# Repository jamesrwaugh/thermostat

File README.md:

# AVR Thermostat

James' interest in making a thermostat

# Features

- [End Goal] Home Assisstant integration compatible
- Plugs into residential connections offering 24VAC power
- Programmable time/day-based temperature settings
- Heating, cooling, and off modes
- Battery-backed storage for settings and time
- Support on-cool and on-heat reverse valve types
- Auto or always-on fan setting
- Display in Fahrenheit or Celsius
- ISP header for firmware flashing and updates
- Objectively gorgeous vacuum-florescent display
- Runs on a familiar, lovable AVR
- All this and more, in a small & tiny 16Kb firmware binary

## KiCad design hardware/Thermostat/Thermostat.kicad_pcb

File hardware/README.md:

# 2.0 Fixes

- [ ] Correct to 1mm hole sizes for screen connector
- [ ] Correct hole placement for buttons
- [ ] 10k Pull-up resistor on RXD of RS-485 (see datasheet)
- [ ] Use a dedicated flash chip, need more than 56 bytes of DS1307
- [ ] Use an analog temperature chip, I2C driver size for TMP116 is 500 bytes, or reduce code size

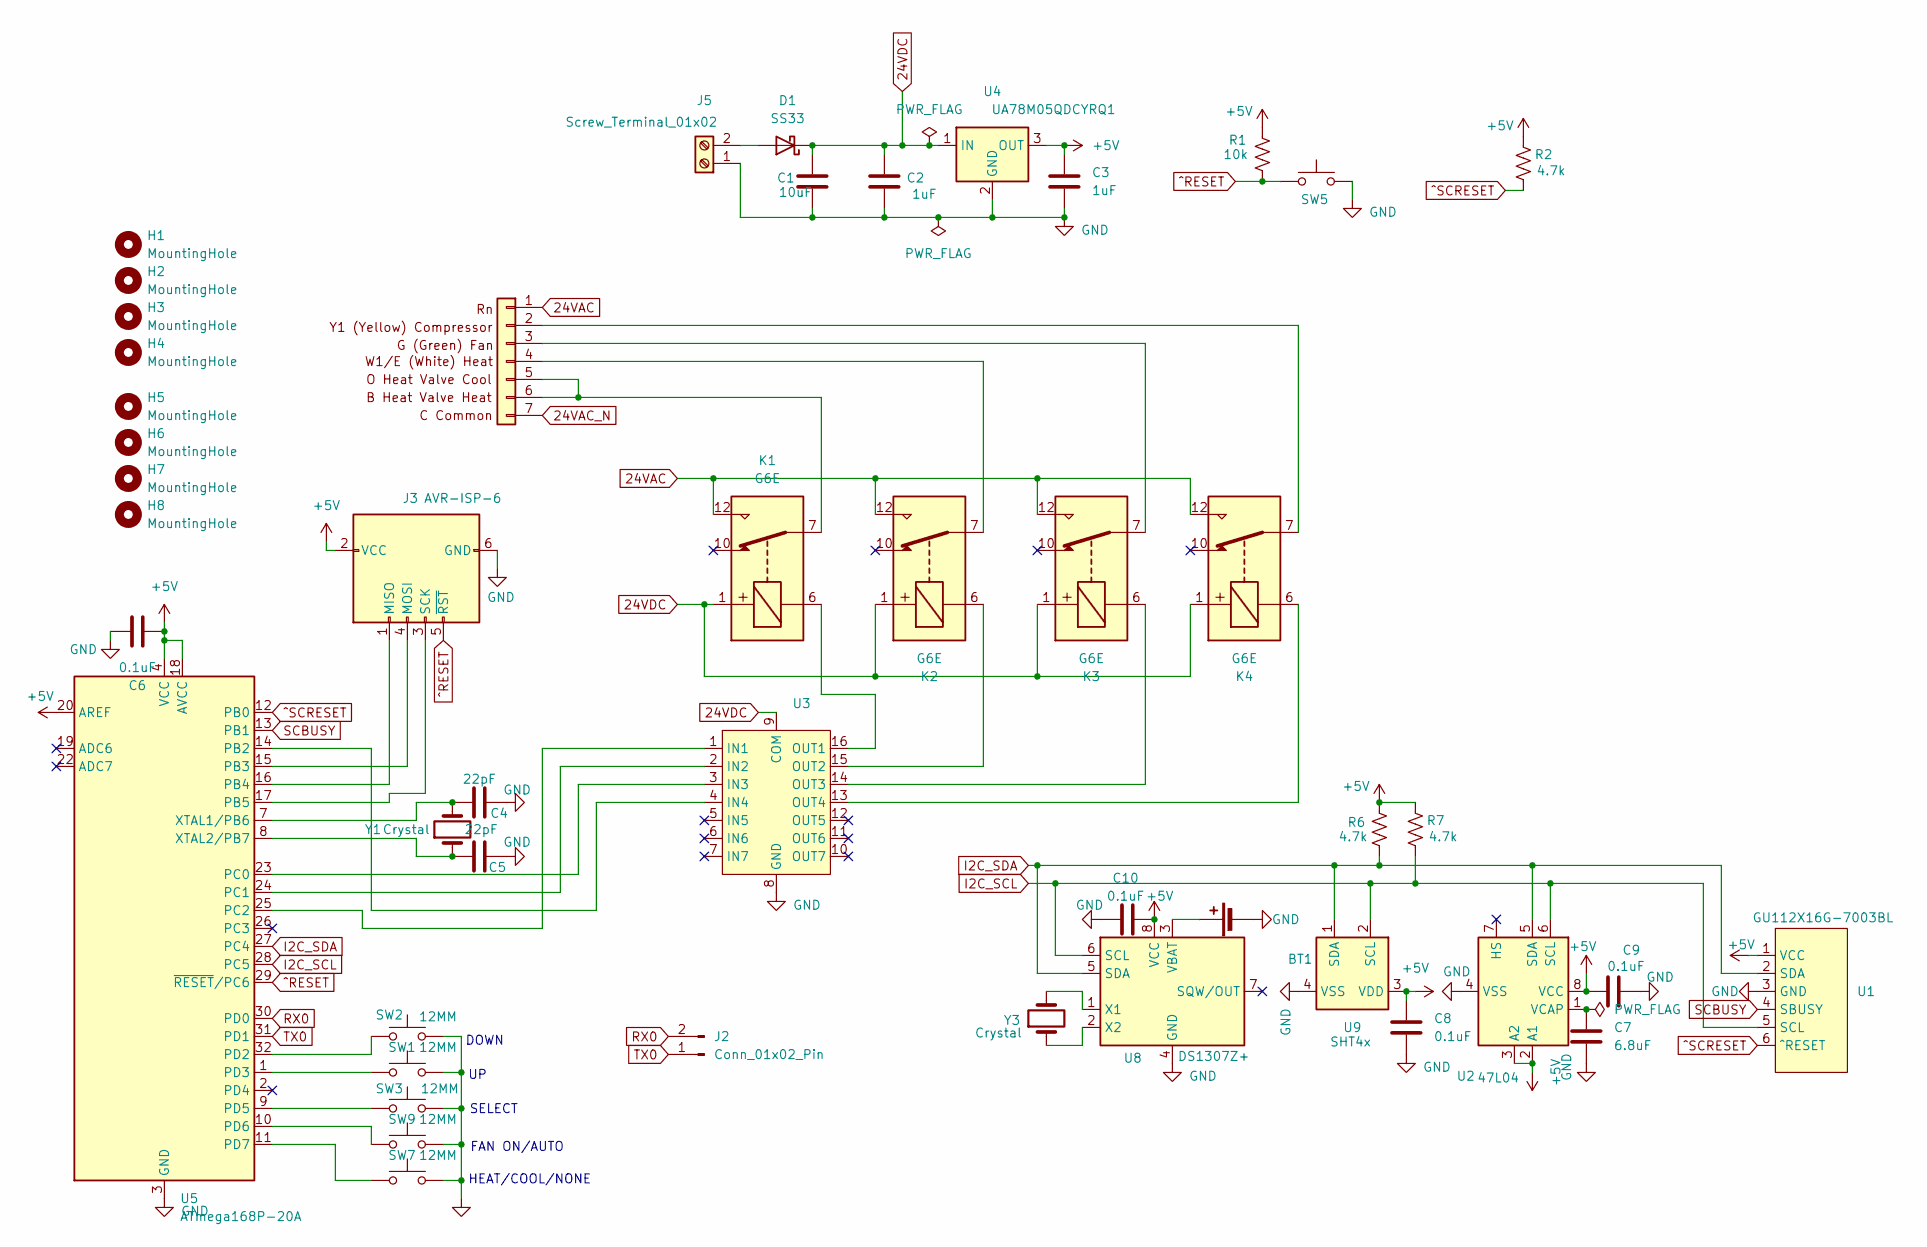
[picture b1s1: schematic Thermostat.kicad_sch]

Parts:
BT1: Battery_Cell; BS-12-B3AA011
C1: 10uF; C_1210_3225Metric
C2, C3: 1uF; C_1210_3225Metric
C4, C5: 22pF; C_0603_1608Metric
C6, C8, C9, C10: 0.1uF; C_0603_1608Metric
C7: 6.8uF; C_0603_1608Metric
D1: SS33; D_SMA
H1, H2, H3, H4: MountingHole; MountingHole_3mm
H5, H6, H7, H8: MountingHole; MountingHole_2mm
J2: Conn_01x02_Pin; PinHeader_1x02_P2.54mm_Vertical_SMD_Pin1Left
J3: AVR-ISP-6; PinHeader_2x03_P2.54mm_Vertical_SMD_2
J4: MainConnectorr; TerminalBlock_MaiXu_MX126-5.0-07P_1x07_P5.00mm
J5: Screw_Terminal_01x02; TerminalBlock_MetzConnect_Type094_RT03502HBLU_1x02_P5.00mm_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
K1, K2, K3, K4: G6E; Relay_SPDT_Omron_G6E
R1: 10k; R_0603_1608Metric
R2, R6, R7: 4.7k; R_0603_1608Metric
SW1, SW2, SW3, SW7, SW9: 12MM; B3F
SW5: SW_Push; SW_Push_1P1T_NO_CK_KMR2
U1: GU112X16G-7003BL; GU-7003
U2: 47L04; SOIC-8_3.9x4.9mm_P1.27mm
U3: SOIC-16_3.9x9.9mm_P1.27mm
U4: UA78M05QDCYRQ1; SOT-223-3_TabPin2
U5: ATmega168P-20A; TQFP-32_7x7mm_P0.8mm
U8: DS1307Z+; SOIC-8_3.9x4.9mm_P1.27mm
U9: SHT4x; Sensirion_DFN-4_1.5x1.5mm_P0.8mm_SHT4x_NoCentralPad
Y1: Crystal; Crystal_SMD_5032-2Pin_5.0x3.2mm
Y3: Crystal; Crystal_SMD_3215-2Pin_3.2x1.5mm

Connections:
24VAC: J4.1, K1.12, K2.12, K3.12, K4.12
24VAC_N: J4.7
24VDC: C1.1, C2.1, D1.1 (K), K1.1, K2.1, K3.1, K4.1, U3.9 (COM), U4.1 (IN)
+5V: C3.1, C6.1, C8.2, C9.2, C10.1, J3.2 (VCC), R1.1, R2.1, R6.1, R7.1, U1.1 (VCC), U2.2 (A1), U2.3 (A2), U2.8 (VCC), U4.3 (OUT), U5.4 (VCC), U5.6 (VCC), U5.18 (AVCC), U5.20 (AREF), U8.8 (VCC), U9.3 (VDD)
GND: BT1.2 (-), C1.2, C2.2, C3.2, C4.1, C5.1, C6.2, C7.2, C8.1, C9.1, C10.2, J3.6 (GND), J5.1, SW1.2, SW2.1, SW3.2, SW5.2, SW7.2, SW9.2, U1.3 (GND), U2.4 (VSS), U3.8 (GND), U4.2 (GND), U5.3 (GND), U5.5 (GND), U5.21 (GND), U8.4 (GND), U9.4 (VSS)
I2C_SCL: R7.2, U1.5 (SCL), U2.6 (SCL), U5.28 (PC5), U8.6 (SCL), U9.2 (SCL)
I2C_SDA: R6.2, U1.2 (SDA), U2.5 (SDA), U5.27 (PC4), U8.5 (SDA), U9.1 (SDA)
unnamed: BT1.1 (+), U8.3 (VBAT)
unnamed: D1.2 (A), J5.2
unnamed: J3.1 (MISO), U5.16 (PB4)
unnamed: J3.4 (MOSI), U5.15 (PB3)
unnamed: J3.3 (SCK), U5.17 (PB5)
unnamed: J4.2, K4.7
unnamed: J4.3, K3.7
unnamed: J4.4, K2.7
unnamed: J4.5, J4.6, K1.7
unnamed: C7.1, U2.1 (VCAP)
unnamed: U3.1 (IN1), U5.25 (PC2)
unnamed: U3.2 (IN2), U5.24 (PC1)
unnamed: U3.3 (IN3), U5.23 (PC0)
unnamed: U3.4 (IN4), U5.14 (PB2)
unnamed: K1.6, U3.16 (OUT1)
unnamed: K2.6, U3.15 (OUT2)
unnamed: K3.6, U3.14 (OUT3)
unnamed: K4.6, U3.13 (OUT4)
unnamed: SW2.2, U5.32 (PD2)
unnamed: SW1.1, U5.1 (PD3)
unnamed: SW3.1, U5.9 (PD5)
unnamed: SW9.1, U5.10 (PD6)
unnamed: SW7.1, U5.11 (PD7)
unnamed: C4.2, U5.7 (XTAL1/PB6), Y1.2
unnamed: C5.2, U5.8 (XTAL2/PB7), Y1.1
unnamed: U8.1 (X1), Y3.2
unnamed: U8.2 (X2), Y3.1
RX0: J2.2, U5.30 (PD0)
SCBUSY: U1.4 (SBUSY), U5.13 (PB1)
TX0: J2.1, U5.31 (PD1)
^RESET: J3.5 (~RST), R1.2, SW5.1, U5.29 (~RESET/PC6)
^SCRESET: R2.2, U1.6 (^RESET), U5.12 (PB0)

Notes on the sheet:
SELECT
HEAT/COOL/NONE
FAN ON/AUTO
DOWN

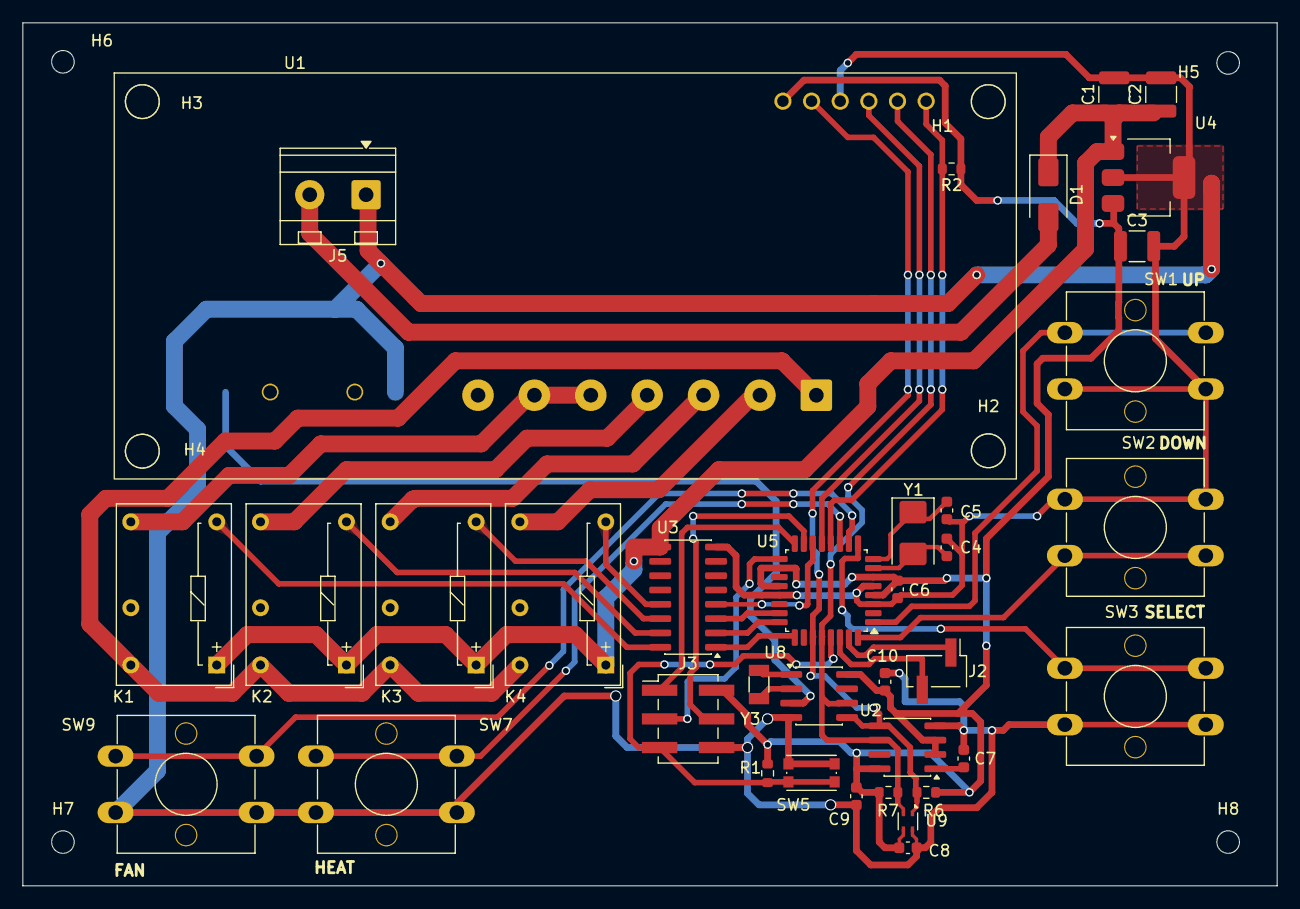
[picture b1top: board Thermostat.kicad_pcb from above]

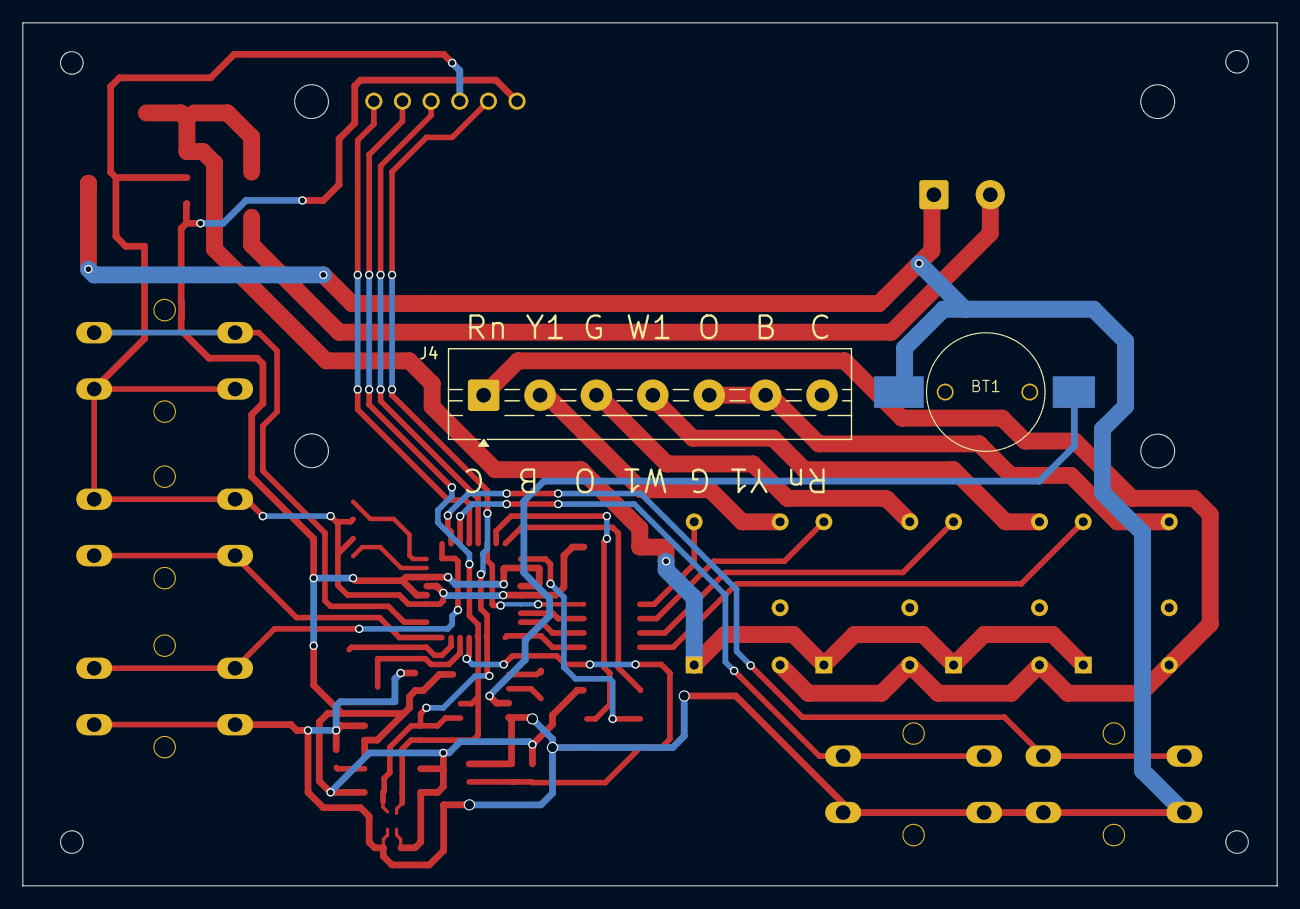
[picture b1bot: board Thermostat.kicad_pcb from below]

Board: 2 copper layers, 111.2 x 76.5 mm, 47 parts (2 on the bottom side), 38 nets.

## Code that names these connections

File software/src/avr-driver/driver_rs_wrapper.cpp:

#include "c_api/driver_rs_wrapper.hpp"

#include <avr/io.h>
#include <avr/sfr_defs.h>
#include <avr/sleep.h>
#include <etl/optional.h>

#include "driver.hpp"

extern "C" {

void DriverInit(const AvrDriverCallbacks& callbacks, void* userData) {
  gDriver.emplace(callbacks, userData);
  gDriver->Setup();
}

void DriverWriteSerialPort(const uint8_t* bytes, uint8_t numBytes) {
  gDriver->Serial_.write(bytes, numBytes);
}

void DriverDisplayTemp(uint8_t temp) {
  auto& screen = gDriver->Screen;
  screen.GU7000_selectWindow(AvrDrivers::Window::LowerRight);
  screen.GU7000_clearScreen();
  screen.GU7000_setCursor(0, 0);
  screen.print(temp);
}

void DriverDisplaySetPoint(uint8_t temp) {
  auto& screen = gDriver->Screen;
  screen.GU7000_selectWindow(AvrDrivers::Window::UpperRight);
  screen.GU7000_clearScreen();
  screen.GU7000_setCursor(0, 0);
  screen.print(temp);
}

void DriverDisplayIsHeating() {
  auto& screen = gDriver->Screen;
  screen.GU7000_selectWindow(AvrDrivers::Window::LowerLeft);
  screen.GU7000_clearScreen();
  screen.GU7000_setCursor(0, 0);
  screen.print("HEAT");
}

void DriverDisplayIsCooling() {
  auto& screen = gDriver->Screen;
  screen.GU7000_selectWindow(AvrDrivers::Window::LowerLeft);
  screen.GU7000_clearScreen();
  screen.GU7000_setCursor(0, 0);
  screen.print("COOL");
}

uint8_t DriverReadTemp() {
  return gDriver->TempSensor.read_temp();
}

void DriverDisplayIsIdle() {
  auto& screen = gDriver->Screen;
  screen.GU7000_selectWindow(AvrDrivers::Window::LowerLeft);
  screen.GU7000_clearScreen();
}

void DriverRelayOn(Relay r) {
  switch (r) {
    case Relay::Fan:
      // PC0
      PORTC |= _BV(PORTC0);
      break;
    case Relay::Compressor:
      // PB2
      PORTB |= _BV(PORTB2);
      break;
    case Relay::Heat:
      // PC1
      PORTC |= _BV(PORTC1);
      break;
    case Relay::ReversingValve:
      // PC2
      PORTC |= _BV(PORTC2);
      break;
  }
}

void DriverRelayOff(Relay r) {
  switch (r) {
    case Relay::Fan:
      // PC0
      PORTC &= ~_BV(PORTC0);
      break;
    case Relay::Compressor:
      // PB2
      PORTB &= ~_BV(PORTB2);
      break;
    case Relay::Heat:
      // PC1
      PORTC &= ~_BV(PORTC1);
      break;
    case Relay::ReversingValve:
      // PC2
      PORTC &= ~_BV(PORTC2);
      break;
  }
}

void DriverMcuSleep() {
  sleep_cpu();
}

void DriverPollInput() {
  gDriver->ReadInput();
}
}

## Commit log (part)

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2024-11-16 Real initial commit :)
2024-11-17 Add lots of stuff
2024-11-17 More random progress
2024-11-17 Lots more hardware progress
2024-11-17 Lots of hardware progress, beginning to place things
2024-11-19 Routing entire board
2024-11-20 Use ATmega88 for fun; wiring tweaks
2024-11-20 More adjusting routes
2024-11-22 Initial Software stack setup with Rust + CPP + Meson
2024-11-22 Solve ERC, re-do power symbol
2024-11-24 New horizons?
2024-11-26 Flesh out a lot more of the stack
2024-11-27 Integrate cbindgen and Cargo into Meson compile command
2024-11-28 Put in 'use' to make sure C API is exported in AVR crate
2024-11-28 Add in Arch-based installation of AVR-LibC for now?
2024-11-29 Fix routes and and ERC
2024-11-30 Tweaks?
2024-11-30 Get in a seemingly-good FSM crate, start to work on Thermostat logic
2024-11-30 Help?
2024-11-30 Helped?
2024-12-01 More wrangling and proving it should work?
2024-12-01 Fuuuuuck
2024-12-02 Give up hopes on C object storage and remove weird undefined behavior with compiler optimizing out
2024-12-03 Start getting in CPP AVR-side software and drivers
2024-12-05 Fix floats accidentially sneaking in with tmp116
2024-12-06 Work in getting wires tied in main.cpp
2024-12-06 More work and get files split out
2024-12-06 Move Relay thing off of ADC7 and re-route
2024-12-09 Get in Arduino Serial; Get in new simavr-toolbox for parts
2024-12-11 Screw around more with software, might just use TCA8418
2025-01-01 Reverse: Start huge refactor to have the Rust code top-level, AVR stuff all CPP And as a library instead of main
2025-01-04 One big WIP a Day
2025-01-04 Bring back Heating events and just put HW stuff back
2025-01-04 Everything compiles?
2025-01-04 Rust compiles and links
2025-01-06 Various WIP; Get switches in; Flesh driver; Start simulator
2025-01-06 Bring in initial flood of code to getting simulator working!
2025-01-06 Add text to pins
2025-01-06 More Code
2025-08-18 Project version update
2025-08-20 Split into multiple files
2025-08-20 Project upgrade, add program button
2025-08-21 simavr-toolbox submodule
2025-08-23 Select button routing
2025-08-23 Avoid insanity in main
2025-08-27 Lots of work on JLCPCB parts
2025-08-29 Much design work
2025-08-31 DS1307; Get in Bitproto for serializing thermo state; fix clangd
2025-08-31 We should be able to sleep. Do it in best practice way
2025-09-01 Fleshing out most things
2025-09-02 Support reverse valve. Change out connector. Put in right parts
2025-09-02 Implement reverse valve type
2025-09-02 No temp repeat
2025-09-03 Fix variables pulling in malloc, free, atexit and more, saving a ton of flash. New DS1307 module next
2025-09-03 New squaredel DS1307 fork, to save flash
2025-09-03 Set magic on smart data init
2025-09-03 clangd lies
2025-09-04 More fleshing out of functionality
2025-09-04 Support reading hardware from static state; split buttons / protos
2025-09-04 Updated protos and start of program state greatness
2025-09-05 Comms event basics, add new protos, premade pipenv environment files for bitproto
2025-09-05 Forgot to turn relays off coming out of cooling
2025-09-06 Flesh out a lot of simulator
2025-09-06 Simulation with UI loads and runs / doesn't immediately crash
2025-09-06 The variant / visitor stuff was cool... but keeping it simple saves 186 bytes flash.
2025-09-06 Put in the comm events where they should go
2025-09-06 Put in SIMULATED macro to get in fake Gu7000 I2C screen, put on simulator, get AI to write UI
2025-09-06 Start fixing bugs. Bring in new simavr-toolbox with FTXUI components. Winning.
2025-09-07 Very sad, forgot to init tmp116
2025-09-07 Starting I2C listener
2025-09-07 Get in I2C listener
2025-09-07 Lots of good simulator work and bug fixes
2025-09-10 Remove absolute insanity in TMP116 conversion and think a little bit for same effect
2025-09-10 Fixing a bunch of bugs and improving simulator
2025-09-10 Hall of fame bugs of I2C setup / reverse valve not setting DDRC pins correctly
2025-09-10 Move loading settings inside thing, properly handle initial fan state
2025-09-11 Support display in Freedom Units, reviving old VLSI lab techniques
2025-09-11 Move out enums so they can be used elsewhere, support sending temp unit
2025-09-14 Flash reduction WIP - Drop ETL debounce, drop userdata, ~300 bytes saved
2025-09-14 Cleanup debounce
2025-09-14 No need for such huge serial buffer size
2025-09-14 WIP: Save a whopping 1470 bytes flash, ripping out ETL hfsm/fsm
2025-09-15 WIP correcting state semantics
2025-09-15 Fix state change bugs of cooling_parent ctor, better SIMULATED
2025-09-18 Expose DS1307 time and get it in to at least measure Flash
2025-09-18 Possible Gu-7000 part?
2025-09-19 WIP: Flash reduction part 3, and Modbus
2025-09-19 Some reasonable AVR optimization flags, mostly -mcall-prologues, saving ~120 bytes flash
2025-09-20 Remove old Comms thing and Screen windows, saving 270 bytes flash
2025-09-21 Let's start writing the program state
2025-09-21 Update README with latest developments
2025-09-21 Put in Hardware README to not forget
2025-12-14 Use 24v barrel jack for now. Fix placement issues with screen and buttons
2025-12-25 Misc fixes for DC power probably
2025-12-25 Screen WIP
2025-12-26 Working on real hardware
2025-12-26 Getting somewhere with the programming...
2025-12-26 Get in screen boxes
2025-12-27 Organize into files
2025-12-27 Put some more boxes in for testing
2025-12-27 Draw character box on second line
2025-12-27 Debugging screen code
2025-12-27 Looks good visually
2025-12-27 Fix issue with boxes displaying out of order
2025-12-27 Acceptable solution for different screens
2025-12-27 Better indicators
2025-12-27 Looks even better on display
2025-12-28 I think the 8k dream is dead
2025-12-28 Init the screen
2025-12-28 Fix bugs
2025-12-28 Integrate programming screens into main app. The 8kB dream is dead. 10kB is possible
2025-12-29 Correct 10ms count thing, remove old window thing
2025-12-29 Some organizing and clean up WIP
2025-12-29 Support adding day of week in config
2025-12-30 Same 234 bytes flash, Come up with a better digit-based solution for programming, instead of converting to-from ascii
2025-12-30 Fix CharSetScreenBox bugs and shoddy AI completion, rename TwoDigitScreenBox
2025-12-30 Properly put in state type
2025-12-30 Unused funcitons
2025-12-31 Cleanup
2025-12-31 Oops
2026-01-02 Fix off on CharSetScreenBox, AM/PM placement
2026-01-06 Some Driver fixes
2026-01-07 atmega168p
2026-01-07 No count needed
2026-01-07 Get Grok to give me a good starter implemtation of Gu7000
2026-01-11 Put back I2C temp since we have 16k flash, put in fake Screen handle thing
2026-01-12 Good progress of Gu7000 simulation
2026-01-12 Clean
2026-01-12 Screen commands working
2026-01-12 Trying to get image to show....
2026-01-13 Use unordered_map for command table instead
2026-01-14 Get rid of fake screen stuff and tie in real working screen! Fix bugs now that we can actually see the screen
2026-01-14 pragma once
2026-01-14 Seeing if program screen will work...
2026-01-14 Get in ProcessCharacterDisplayAtPosition, fix OOBs, uninits
2026-01-15 Fix issue with drawing floating characters not advancing
2026-01-15 add .zed
2026-01-15 Formatting
2026-01-17 Goodbye old screen test code
2026-01-18 Some work on what is to come on programming maybe
2026-01-22 Inching closer and closer
2026-01-24 Wiring / DRC / JLCPCB
2026-01-24 Busy pin
2026-01-24 No more Modbus
2026-01-24 Software updates to match new hardware
2026-01-24 Honest README
2026-01-24 Some labels
2026-01-24 Correct pin configs
2026-01-25 Cleaning up and getting in Home Assistant stuff in
2026-01-25 Home Assist WIP
2026-01-25 Remove unfortunate relic
2026-01-25 HomeAst integration deeper...
2026-01-25 HomeAst....
2026-01-26 More HomeAssist telemetry
2026-01-26 Move a bunch of heating-only stuff to CoolableParent
2026-01-26 Fix UI widths
2026-01-26 Fix date positions
2026-01-27 Bring out images and add some new ones, Possible I2C init bug or sim bug, show Screen in FTXUI fancy canvas
2026-01-27 More perfected screen UI, more perfected display format, get in toolbox changes
2026-01-29 PoC MQTT-C
2026-01-30 Better display stuff WIP
2026-01-30 Save 130 bytes of flash or something
2026-01-30 Even better
2026-01-31 Realize from real-world experiment that relay coils are directional, and fix
2026-02-01 Initial commit of ESP32 side
2026-02-01 Fix merge issues, images were moved to driver
2026-02-01 I am appaled at a Hello World with Rust esp_hal taking 395kB of flash
2026-02-01 No more MQTT in Avr
2026-02-02 Get Bitprotos into Rust
2026-02-02 Get BitProtos back in
2026-02-04 Safer save data, memcpy bitproto, mqtt connection stuff
2026-02-04 More proper integrations on state loading
2026-02-04 Checksum standards
2026-02-04 Start simulator serial HaCommand callback
2026-02-06 Move out GU7000 into simavr-toolbox
2026-02-07 Temperature....
2026-02-07 Integrate wrapped temperature
2026-02-07 Morning extermination
2026-02-07 Back to base 2
2026-02-07 Better README
2026-02-07 Update simavr-toolbox
2026-02-07 Use and add proper temperature tolerances instead of weird state change timeouts
2026-02-07 Clangd format to wrap fluent calls
2026-02-07 Reuse code
2026-02-07 Get time/date out of save data and use DS1307 directly
2026-02-07 Fixed time setting year bug
2026-02-07 Convert to x512 for more range, and fix some bugs
2026-02-08 Finally stop clangd from adding <cstdint.h>
2026-02-08 Get in SH4X
2026-02-08 Add FTDI-based I2C tester for GU7000
2026-02-08 Soon, scrolling up images
2026-02-09 Scoll-o-mania
2026-02-09 It is beautiful, but it may never see the light of day
2026-02-10 Scrolling victory
2026-02-11 Getting scrollers into App
2026-02-11 Brightness is good
2026-02-12 Getting scrollers in WIP
2026-02-12 Working on complete UI...
2026-02-12 Render WIP
2026-02-12 I think we finally got the data model down
2026-02-12 Keep going...
2026-02-12 I think we got it?
2026-02-13 We got it
2026-02-13 Better use of typedefs
2026-02-13 Move components out into separate files
2026-02-13 Let's go
2026-02-14 Get in cold and idle images
2026-02-14 Make rendering stuff much more memory-efficient by not storing copy of image in Scroller
2026-02-14 Move out MQTT
2026-02-14 Work on moving images to __flash
2026-02-14 Added in new Image C library to place images in Flash memory and isolate damage
2026-02-14 Better clang format
2026-02-14 One more bug before bed
2026-02-14 Fix various bugs
2026-02-14 Solve more bugs and introduce friction into scrolling
2026-02-14 I like this a little better
2026-02-15 Fix ghost errors in clangd
2026-02-15 GCC 14 does not support binary ticks?
2026-02-15 Fix overflow/underflow bugs, sign bugs, casting bugs, hopefully all in Temperature / Humidity
2026-02-16 More integer type bugs solved
2026-02-16 More edge case bugs fixed
2026-02-16 Humidity too
2026-02-16 Forgot to remove a volatile. 240 bytes saved
2026-02-16 Fix setpoint printing put, remove old header, prevent SHT4 overflow
2026-02-18 100 byte flash reduction around rendering stuff, WIP on temperature bug fixes
2026-02-19 Possible solve edge cases in C and F in heating/cooling by 3/8ths and displaying accurate results
2026-02-19 Let's round here too
2026-02-20 218 byte Various reductions in flash, noinline on temperature functions saved a lot
2026-02-20 Put configs closer to usage site
2026-02-20 Everything ScreenConfig const
2026-02-21 Save 22 bytes flash with DrawHeatingStatus
2026-02-22 Good battery and connector layout
2026-02-22 Format HaCommand and fix some bugs from it
2026-02-22 Always changes
2026-02-22 Match screen display with HA sending, better UI
2026-02-22 Update toolbox
2026-03-05 Rust gets nuked again. Bring in CPP and esp-idf for comms. Set up clangd
2026-03-05 ESP32C3
2026-03-08 Start with a base Wifi project
2026-03-08 States...
2026-03-09 Package more code into state machine
2026-03-09 Flesh out events and states more
2026-03-10 Comms progress
2026-03-12 IDF update and compile
2026-03-12 Get in ETL and start of machine machinery
2026-03-12 We don't need 64k
2026-03-13 UART soon
2026-03-13 More soon
2026-03-19 Fixes from Cyber City Circuits review
2026-03-19 Remove physical Reverse Valve button and put it in save state instead
2026-03-19 Update READMEs
2026-03-20 Put switches in order and move resistor
2026-05-11 Hardware work
2026-05-11 Bring in latest Temperature changes from Washer
2026-05-11 New Mibi Tool with 2^8 factor
